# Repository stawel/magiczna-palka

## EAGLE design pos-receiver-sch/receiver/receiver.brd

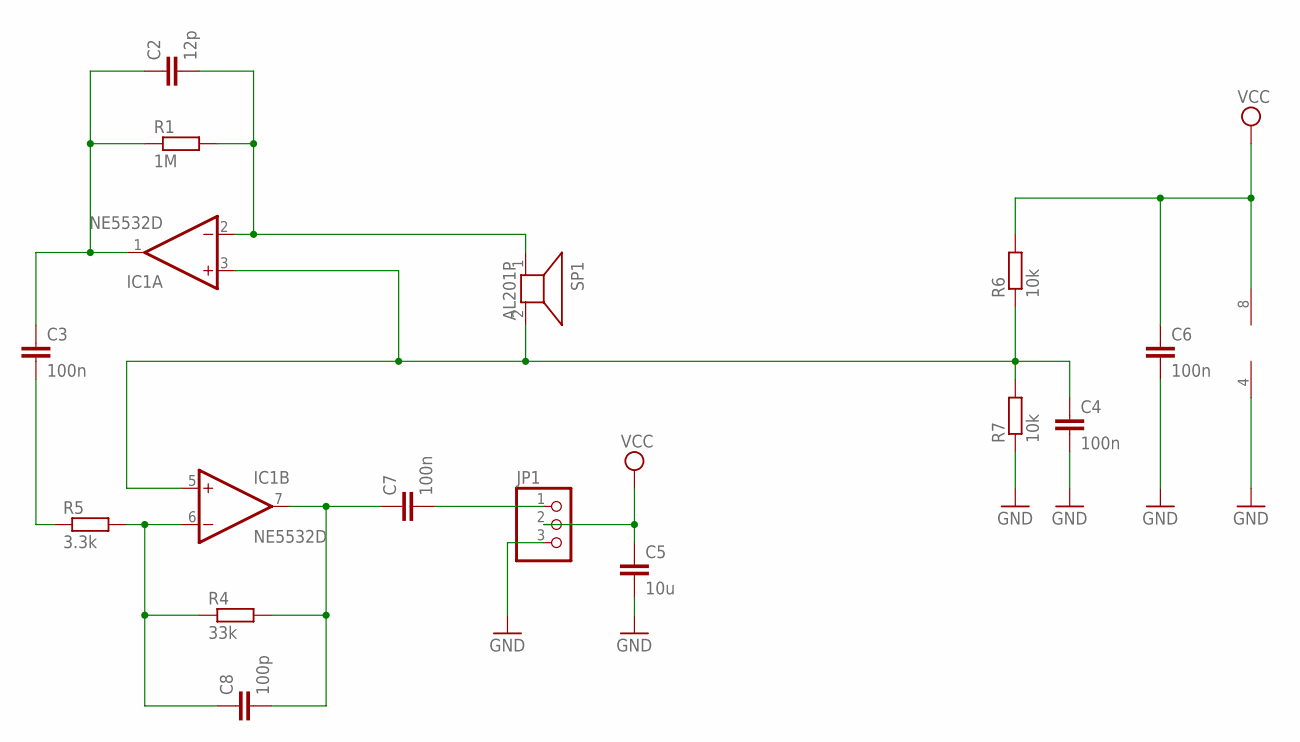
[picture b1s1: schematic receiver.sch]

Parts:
C2: 12p; C0805
C3, C4: 100n; C0805
C5: 10u; C0805
C6: 100n; C1206
C7: 100n; C1206K
C8: 100p; C0805
IC1: NE5532D; SO08
JP1: PINHD-1X3; 1X03
R1: 1M; R0805
R4: 33k; R0805
R5: 3.3k; R0805
R6, R7: 10k; R0805
SP1: AL201P

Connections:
GND: C4.2, C5.2, C6.2, IC1.4 (V-), JP1.3, R7.1
unnamed: C7.2, JP1.1
unnamed: C2.2, IC1.2 (-IN), R1.2, SP1.1
unnamed: C8.1, IC1.6 (-IN), R4.1, R5.2
unnamed: C7.1, C8.2, IC1.7 (OUT), R4.2
unnamed: C3.2, R5.1
unnamed: C2.1, C3.1, IC1.1 (OUT), R1.1
unnamed: C4.1, IC1.3 (+IN), IC1.5 (+IN), R6.1, R7.2, SP1.2
VCC: C5.1, C6.1, IC1.8 (V+), JP1.2, R6.2

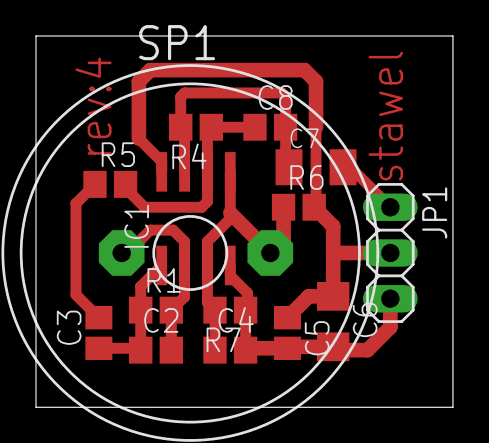
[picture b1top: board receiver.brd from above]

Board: 2 copper layers, 23.2 x 20.6 mm, 15 parts (0 on the bottom side), 9 nets.

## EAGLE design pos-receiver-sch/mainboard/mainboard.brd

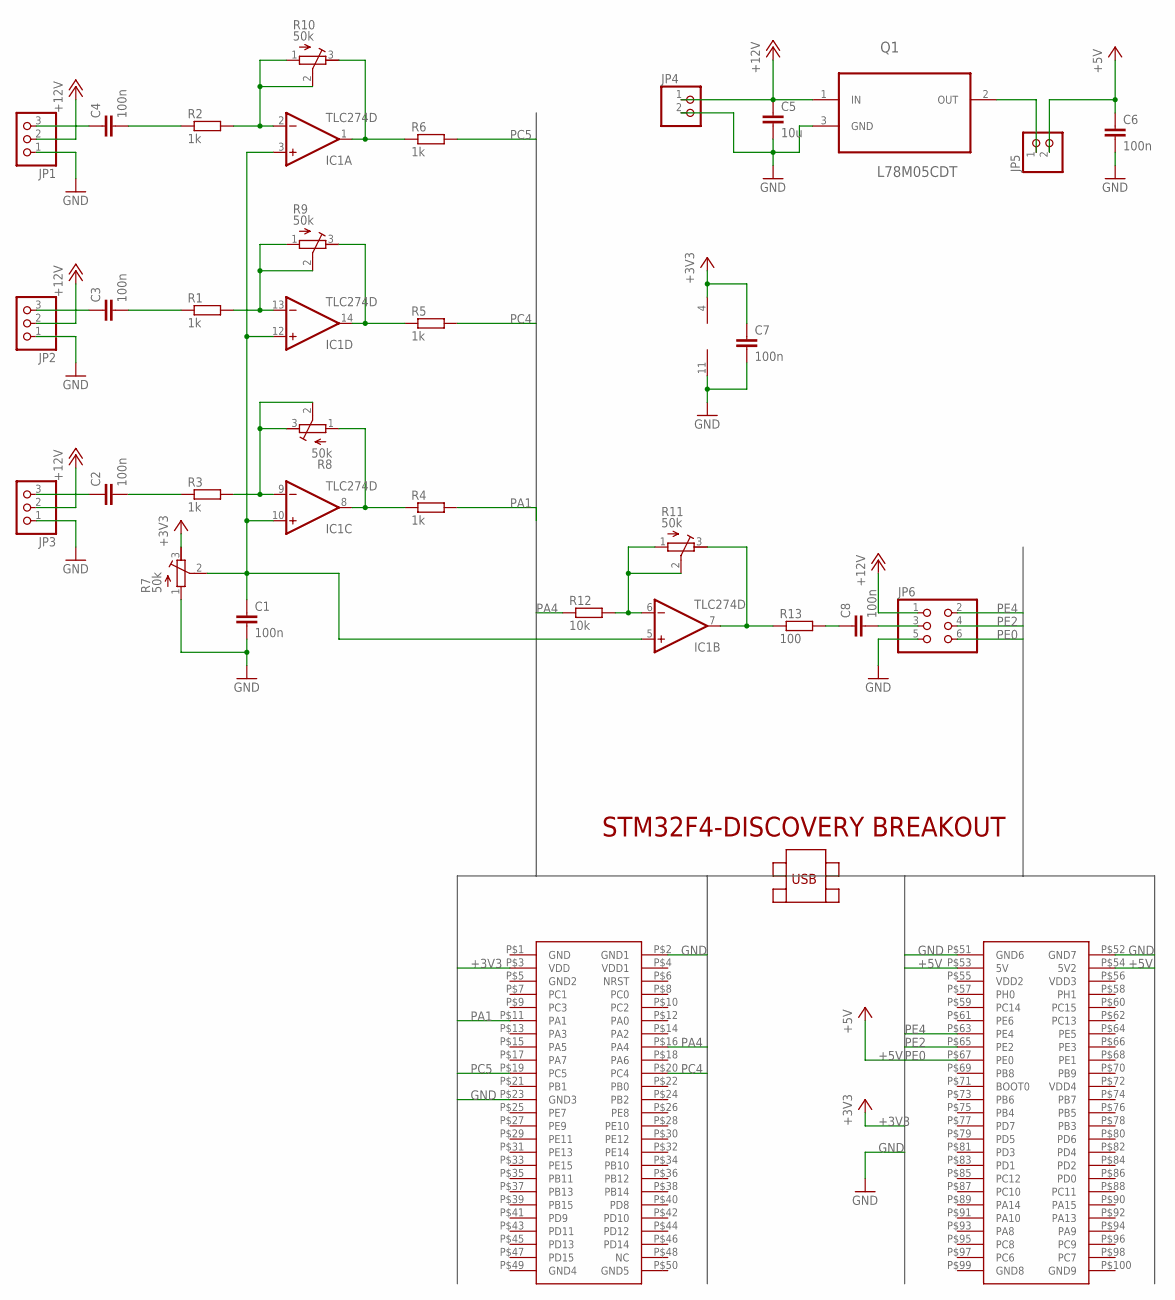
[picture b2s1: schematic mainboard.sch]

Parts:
C1, C2, C3, C4, C6, C7, C8: 100n; C1206K
C5: 10u; C1206K
IC1: TLC274D; SO14
JP1, JP2, JP3: PINHD-1X3; 1X03
JP4, JP5: PINHD-1X2; 1X02
JP6: PINHD-2X3; 2X03
Q1: L78M05CDT; TO225P972X240-3N
R1, R2, R3, R4, R6: 1k; M0805
R5: 1k; R1206
R7, R8, R9, R10, R11: 50k; RTRIM3314J
R12: 10k; M1206
R13: 100; M0805
U$1: STM32F4-DISCOVERY

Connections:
+3V3: C7.1, IC1.4 (V+), R7.3 (A), U$1.P$3 (VDD)
+5V: C6.1, JP5.2, U$1.P$53 (5V), U$1.P$54 (5V2)
+12V: C5.1, JP1.2, JP2.2, JP3.2, JP4.1, JP6.1, Q1.1 (IN)
GND: C1.2, C5.2, C6.2, C7.2, IC1.11 (V-), JP1.1, JP2.1, JP3.1, JP4.2, JP6.5, Q1.3 (GND), R7.1 (E), U$1.P$2 (GND1), U$1.P$23 (GND3), U$1.P$51 (GND6), U$1.P$52 (GND7)
unnamed: JP5.1, Q1.2 (OUT)
unnamed: IC1.6 (-IN), R11.1 (E), R11.2 (S), R12.2
unnamed: IC1.13 (-IN), R1.2, R9.1 (E), R9.2 (S)
unnamed: IC1.1 (OUT), R6.1, R10.3 (A)
unnamed: IC1.8 (OUT), R4.1, R8.1 (E)
unnamed: C2.2, R3.1
unnamed: C2.1, JP3.3
unnamed: C3.1, JP2.3
unnamed: C4.1, JP1.3
unnamed: C4.2, R2.1
unnamed: IC1.7 (OUT), R11.3 (A), R13.1
unnamed: IC1.14 (OUT), R5.1, R9.3 (A)
unnamed: C3.2, R1.1
unnamed: C1.1, IC1.3 (+IN), IC1.5 (+IN), IC1.10 (+IN), IC1.12 (+IN), R7.2 (S)
unnamed: C8.2, JP6.3
unnamed: C8.1, R13.2
unnamed: IC1.2 (-IN), R2.2, R10.1 (E), R10.2 (S)
unnamed: IC1.9 (-IN), R3.2, R8.2 (S), R8.3 (A)
PA1: R4.2, U$1.P$11 (PA1)
PA4: R12.1, U$1.P$16 (PA4)
PC4: R5.2, U$1.P$20 (PC4)
PC5: R6.2, U$1.P$19 (PC5)
PE0: JP6.6, U$1.P$67 (PE0)
PE2: JP6.4, U$1.P$65 (PE2)
PE4: JP6.2, U$1.P$63 (PE4)

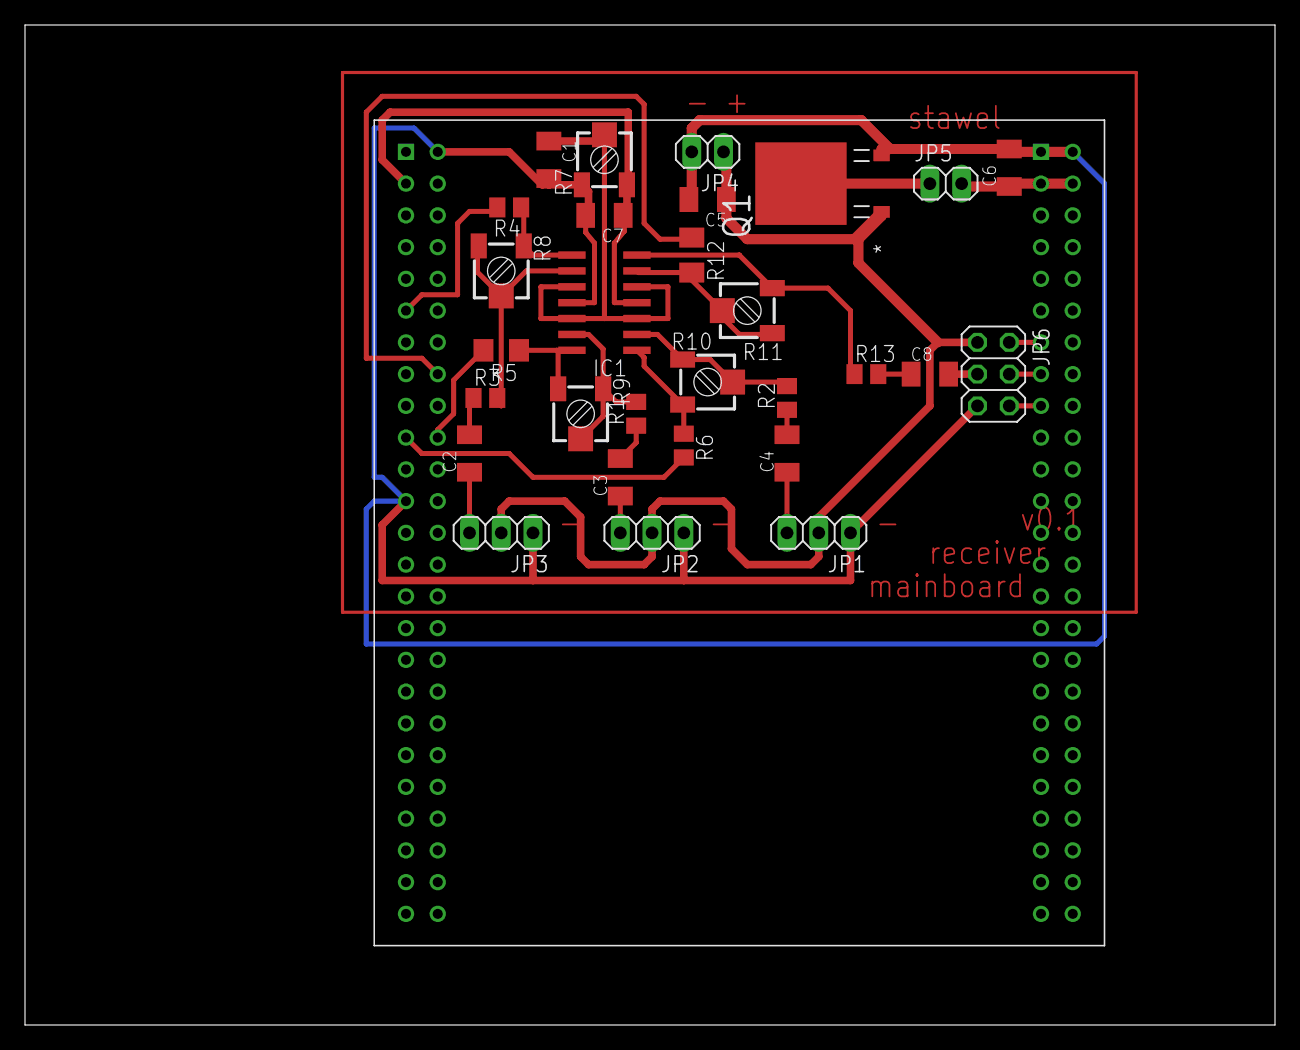
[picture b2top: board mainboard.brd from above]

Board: 2 copper layers, 100.0 x 80.0 mm, 30 parts (0 on the bottom side), 29 nets.

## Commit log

2013-11-24 3rd-party
2013-11-24 add: CMakeList
2013-11-28 3rd-party jeszcze raz
2013-11-28 pierwsza kompilacja
2013-11-28 dodanie skryptu programujacego
2013-11-29 test
2013-11-30 jakas transmisja
2013-11-30 simple oscilloscope
2013-12-01 DMA interrupt handler
2013-12-01 oscy z triggerem
2013-12-01 3d point
2013-12-05 schematy do odbiornika
2013-12-05 rysowanie
2013-12-07 uruchomienie 3 nadajników
2013-12-07 jedno API
2013-12-07 add time_info
2013-12-10 zmiany w schemacie
2013-12-10 receiver-sch ver: 0.2
2013-12-14 get_data_first_max2
2013-12-14 3x signals
2013-12-15 mainboard
2013-12-23 old transmitter code
2013-12-23 test fft
2013-12-23 freq scan
2013-12-23 balwan
2014-01-05 add: test_get_9x_data.py
2014-01-05 get_position_mm
2014-01-05 3x 3D point
2014-01-06 com in separate thread
2014-01-06 exit com thread
2014-01-06 add: time_info
2014-01-06 move to np.array
2014-01-08 removing data_first_max
2014-01-11 removing find_max_data
2014-01-11 remove get_gamma
2014-01-11 distance
2014-01-11 product
2014-01-12 tests
2014-01-12 add: 4-th speaker
2014-01-23 4x trasmitter
2014-01-23 4 transmitter
2014-01-23 sign filter
2014-01-23 speed_limit
2014-01-23 speedlimit
2014-01-28 charge amp
2014-02-14 przed usunięciem błędy kwadratowego
2014-02-15 balwan 1x2
2014-02-16 nowy kabel
2014-02-17 kolejność + mp3d.info
2014-02-17 poprawka
2014-02-17 ply file
2014-08-22 mgr kile project
2014-08-29 wprowadzenie 1.
2015-03-22 bugfix: brak patterns.pkl
2015-05-23 zmiany
2015-05-24 zmiana
2015-05-25 10-test-error
2015-05-26 blad_korel
2015-09-01 biblio
2015-09-05 przecinki
2015-09-05 rysunki z duzej litery
2015-09-06 widoki
2015-09-20 zimana
2015-09-21 kopia
2015-09-21 ania1
2015-09-21 ania2
2015-09-21 ania 4
2015-09-21 ania5
2015-09-21 ania3
2015-09-22 ania7
2015-09-24 zalaczniki
2015-10-09 teoria corekta
2015-10-09 trojkat
2015-10-09 trojkat ok
2015-10-09 nadajnik
2015-10-10 do sprawdzenia
2015-10-10 sygnal wyjsciowy
2015-10-10 odebrany sygnal
2015-10-10 blad korelacji
2015-10-10 kalib
2015-10-11 zamiana "t" z "x"
2015-10-12 wprowadzenie
2015-10-12 szerokości
2015-10-12 mgr_strony
2015-10-13 Imported from https://stawel@github.com/stawel/magiczna-palka.git
2015-10-13 zmiany - xyz.py
2015-10-13 ania: wprow
2015-10-13 ania 2
2015-10-13 ania: mp3d
2015-10-13 korekta dziwna
2015-10-13 obrazek
2015-10-19 str. 1
2015-10-20 promotor: wprowadzenie
2015-10-20 teoria
2015-10-20 odbiornik
2015-10-20 usuniecie textit przy wzorcach
2015-10-20 dla t = 0..m-n
2015-10-20 zmiana z w(x) na w(t)
2015-10-21 soft
2015-10-21 samogloski
2015-10-21 samogl
2015-10-21 poprawki
2015-10-21 kontrowersyjne zmiany
2015-10-21 o ryjowkach
2015-10-22 ostatnie zmiany
2015-10-22 praca
